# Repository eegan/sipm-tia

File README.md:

# sipm-tia
Transimpedance amplifiers for 4 SiPMs

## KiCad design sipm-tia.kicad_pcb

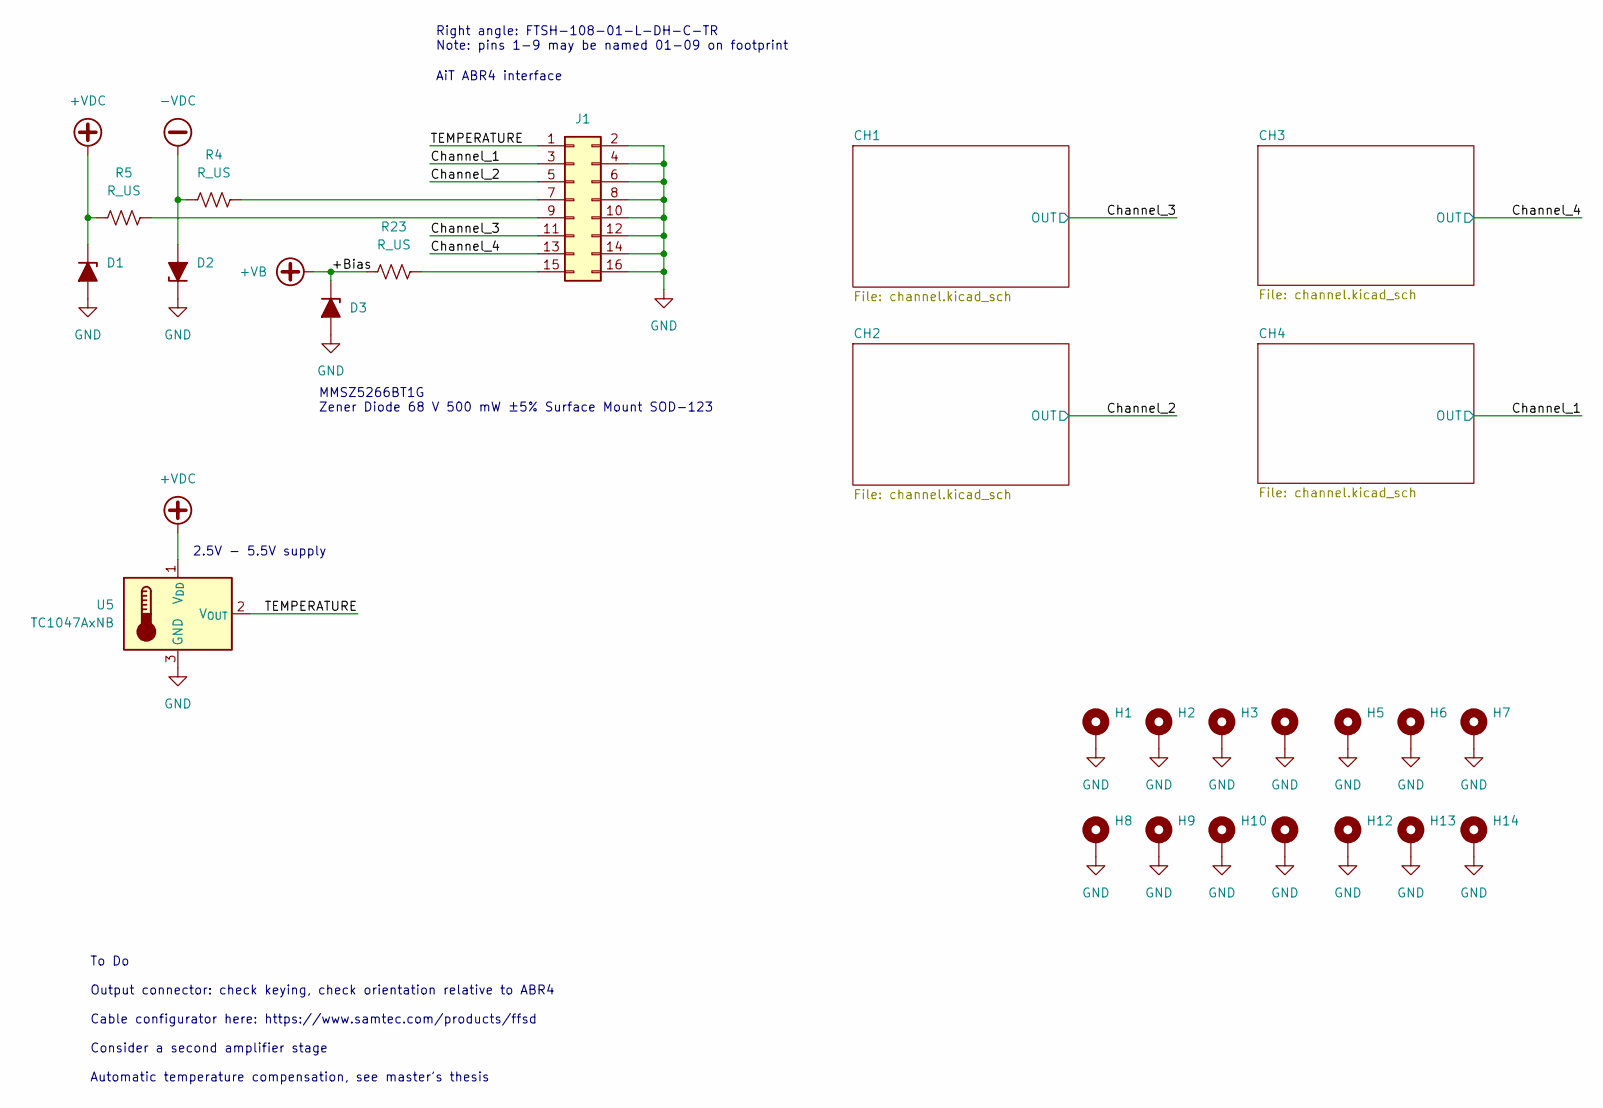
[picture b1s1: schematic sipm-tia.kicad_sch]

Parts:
D1, D2: D_Zener_Filled; D_SOD-123
D3: D_Zener_Filled; D_SOD-123; MPN MMSZ5266BT1G
H1, H2, H3, H4, H5, H6, H7, H8, H9, H10, H11, H12, H13, H14: MountingHole_Pad; MountingHole_3.2mm_M3_Pad
J1: Conn_02x08_Odd_Even; SAMTEC_FTSH-108-01-L-DH-C-TR; MPN FTSH-108-01-L-DH-C-TR
R4, R5, R23: R_US; R_0603_1608Metric
U5: TC1047AxNB; SOT-23; MPN TC1047AVNBTR

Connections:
+VB: D3.1 (K), R23.1; also elsewhere on the board
+VDC: D1.1 (K), R5.1, U5.1 (V_{DD}); also elsewhere on the board
-VDC: D2.2 (A), R4.1; also elsewhere on the board
/Channel_1: J1.3; also elsewhere on the board
/Channel_2: J1.5; also elsewhere on the board
/Channel_3: J1.11; also elsewhere on the board
/Channel_4: J1.13; also elsewhere on the board
/TEMPERATURE: J1.1, U5.2 (V_{OUT})
GND: D1.2 (A), D2.1 (K), D3.2 (A), H1.1, H2.1, H3.1, H4.1, H5.1, H6.1, H7.1, H8.1, H9.1, H10.1, H11.1, H12.1, H13.1, H14.1, J1.2, J1.4, J1.6, J1.8, J1.10, J1.12, J1.14, J1.16, U5.3 (GND); also elsewhere on the board
unnamed: J1.7, R4.2
unnamed: J1.9, R5.2
unnamed: J1.15, R23.2

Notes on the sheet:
To Do Output connector: check keying, check orientation relative to ABR4 Cable configurator here: https://www.samtec.com/products/ffsd Consider a second amplifier stage Automatic temperature compensation, see master's thesis
Right angle: FTSH-108-01-L-DH-C-TR Note: pins 1-9 may be named 01-09 on footprint
AiT ABR4 interface
2.5V - 5.5V supply
MMSZ5266BT1G Zener Diode 68 V 500 mW ±5% Surface Mount SOD-123

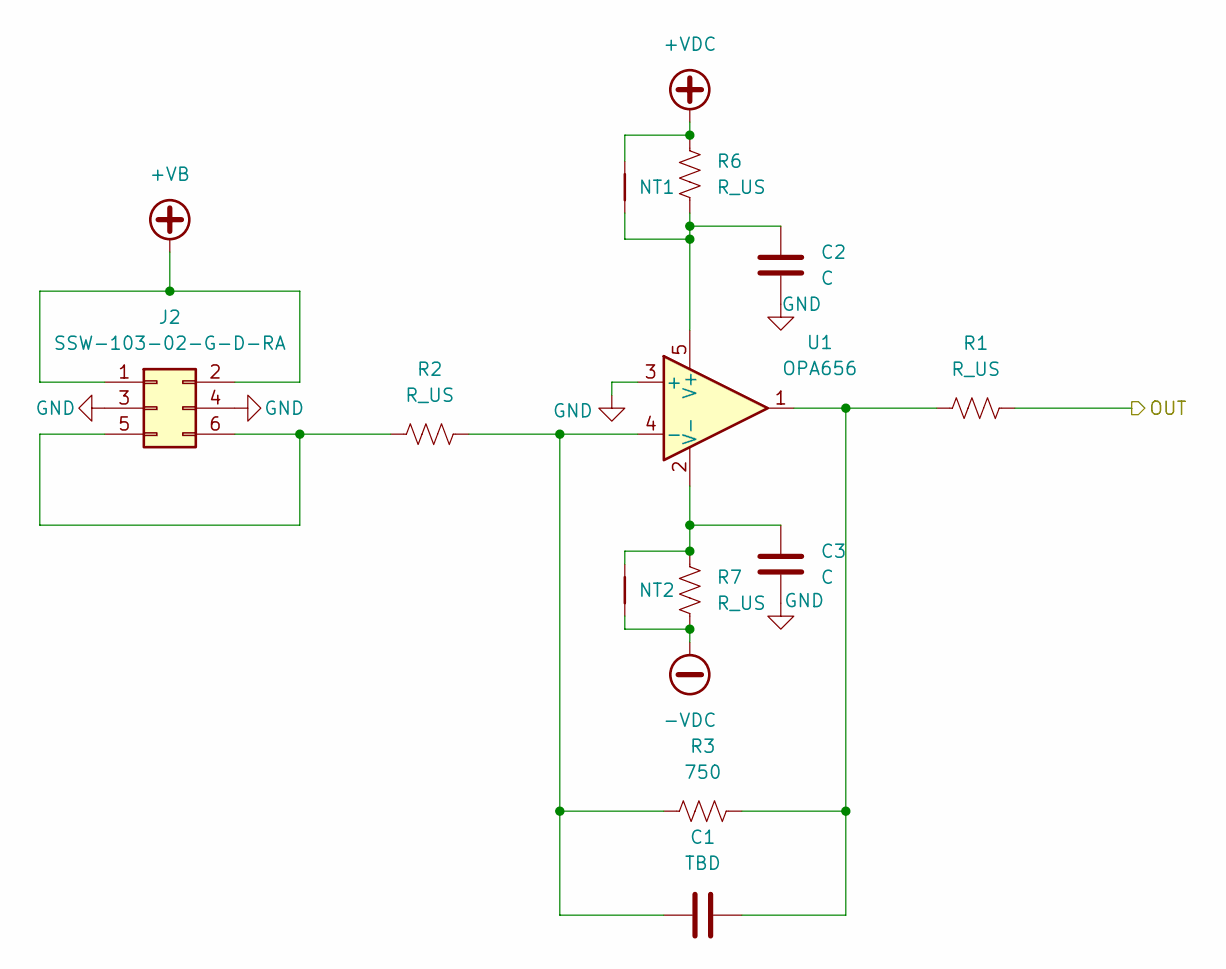
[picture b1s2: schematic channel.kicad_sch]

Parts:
C1: TBD; C_0603_1608Metric_Pad1.08x0.95mm_HandSolder
C2, C3: C; C_0603_1608Metric_Pad1.08x0.95mm_HandSolder
J2: SSW-103-02-G-D-RA; PinSocket_2x03_P2.54mm_Vertical; MPN SSW-103-02-G-D
NT1, NT2: NetTie_2; NetTie-2_SMD_Pad0.5mm
R1, R2, R6, R7: R_US; R_0603_1608Metric_Pad0.98x0.95mm_HandSolder
R3: 750; R_0603_1608Metric_Pad0.98x0.95mm_HandSolder
U1: OPA656; SOT-23-5

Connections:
+VB: J2.1, J2.2; also elsewhere on the board
+VDC: NT1.2, R6.2; also elsewhere on the board
-VDC: NT2.1, R7.1; also elsewhere on the board
/Channel_3: R1.2; also elsewhere on the board
GND: C2.1, C3.1, J2.3, J2.4, U1.3 (+); also elsewhere on the board
unnamed: C1.1, R1.1, R3.2, U1.1
unnamed: J2.5, J2.6, R2.1
unnamed: C1.2, R2.2, R3.1, U1.4 (-)
unnamed: C2.2, NT1.1, R6.1, U1.5 (V+)
unnamed: C3.2, NT2.2, R7.2, U1.2 (V-)

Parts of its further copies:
C4, C5, C7, C8, C10, C11: C; C_0603_1608Metric_Pad1.08x0.95mm_HandSolder
C6, C9, C12: TBD; C_0603_1608Metric_Pad1.08x0.95mm_HandSolder
J3, J4, J5: SSW-103-02-G-D-RA; PinSocket_2x03_P2.54mm_Vertical; MPN SSW-103-02-G-D
NT3, NT4, NT5, NT6, NT7, NT8: NetTie_2; NetTie-2_SMD_Pad0.5mm
R8, R9, R10, R11, R13, R14, R15, R16, R18, R19, R20, R21: R_US; R_0603_1608Metric_Pad0.98x0.95mm_HandSolder
R12, R17, R22: 750; R_0603_1608Metric_Pad0.98x0.95mm_HandSolder
U2, U3, U4: OPA656; SOT-23-5

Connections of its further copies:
+VB: J3.1, J3.2, J4.1, J4.2, J5.1, J5.2; also elsewhere on the board
+VDC: NT3.2, NT5.2, NT7.2, R8.2, R13.2, R18.2; also elsewhere on the board
-VDC: NT4.1, NT6.1, NT8.1, R11.1, R16.1, R21.1; also elsewhere on the board
/Channel_1: R19.2; also elsewhere on the board
/Channel_2: R9.2; also elsewhere on the board
/Channel_4: R14.2; also elsewhere on the board
GND: C4.1, C5.1, C7.1, C8.1, C10.1, C11.1, J3.3, J3.4, J4.3, J4.4, J5.3, J5.4, U2.3 (+), U3.3 (+), U4.3 (+); also elsewhere on the board
unnamed: C6.1, R9.1, R12.2, U2.1
unnamed: C9.1, R14.1, R17.2, U3.1
unnamed: C12.1, R19.1, R22.2, U4.1
unnamed: J3.5, J3.6, R10.1
unnamed: J4.5, J4.6, R15.1
unnamed: J5.5, J5.6, R20.1
unnamed: C6.2, R10.2, R12.1, U2.4 (-)
unnamed: C4.2, NT3.1, R8.1, U2.5 (V+)
unnamed: C5.2, NT4.2, R11.2, U2.2 (V-)
unnamed: C9.2, R15.2, R17.1, U3.4 (-)
unnamed: C7.2, NT5.1, R13.1, U3.5 (V+)
unnamed: C8.2, NT6.2, R16.2, U3.2 (V-)
unnamed: C12.2, R20.2, R22.1, U4.4 (-)
unnamed: C10.2, NT7.1, R18.1, U4.5 (V+)
unnamed: C11.2, NT8.2, R21.2, U4.2 (V-)

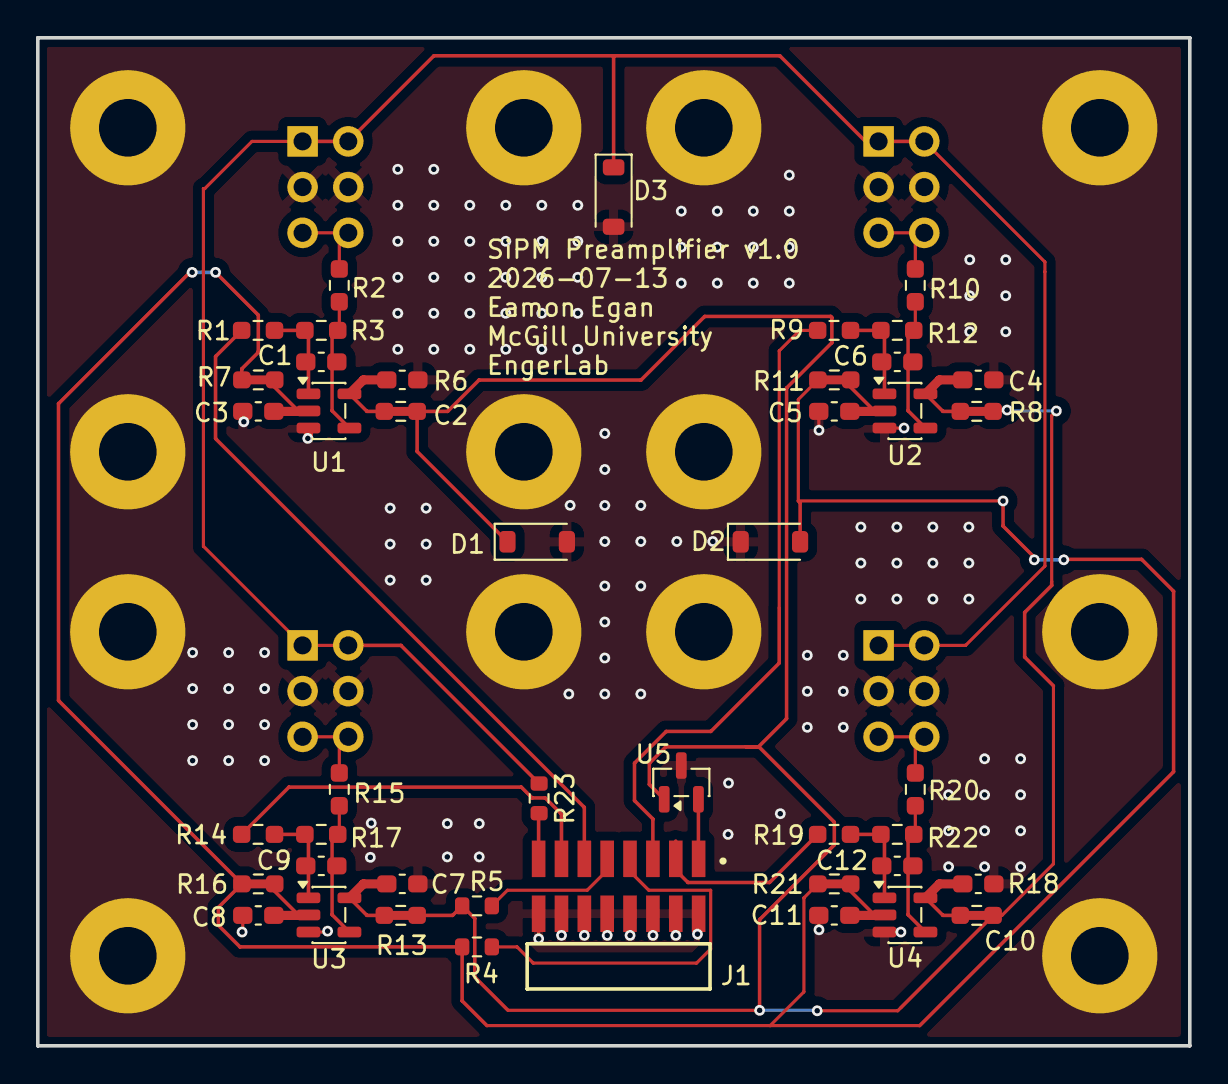
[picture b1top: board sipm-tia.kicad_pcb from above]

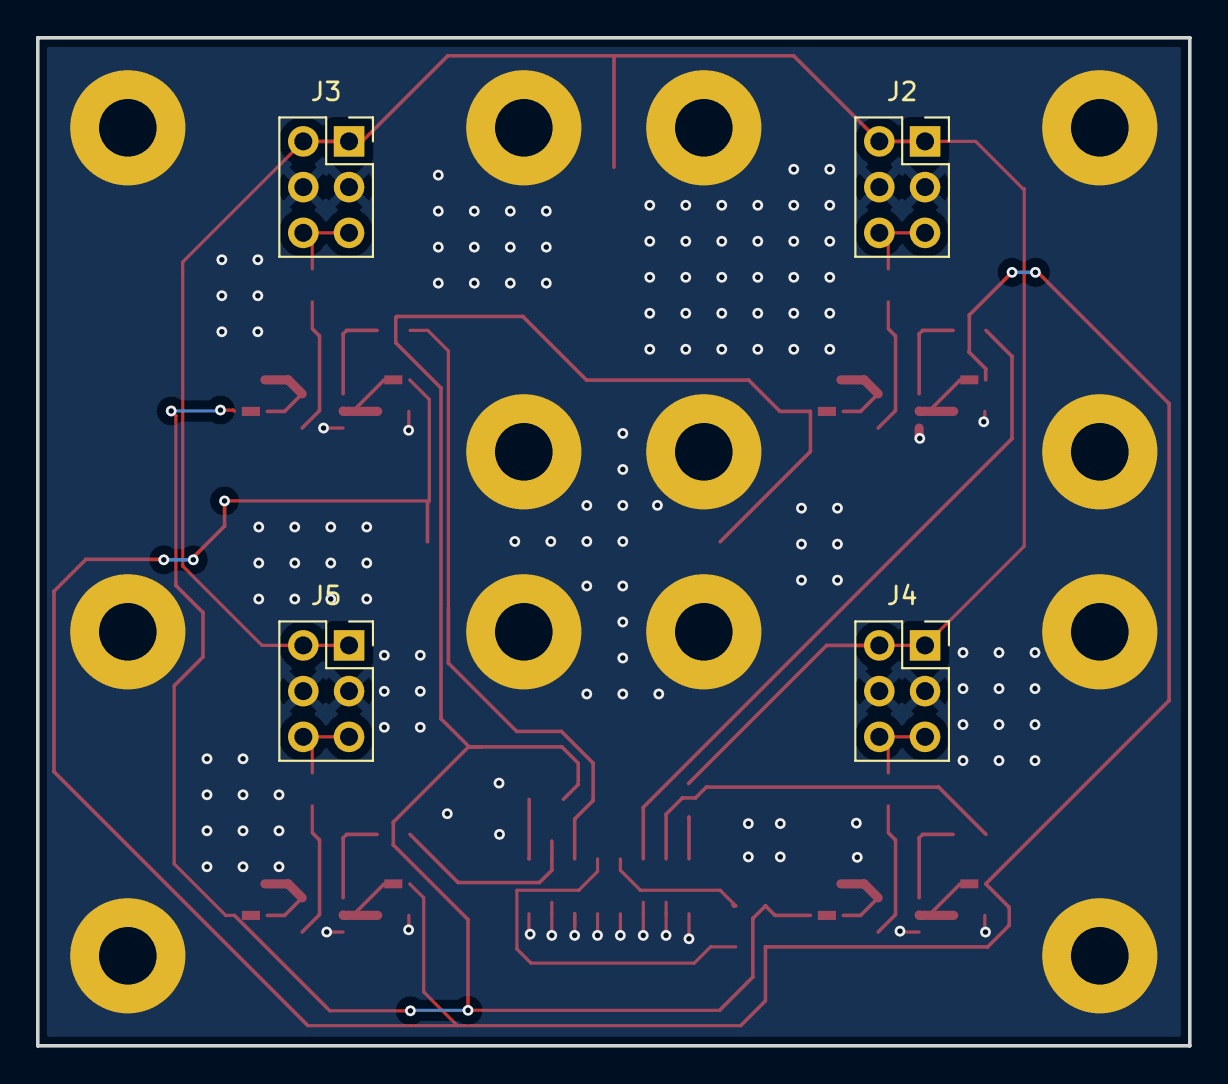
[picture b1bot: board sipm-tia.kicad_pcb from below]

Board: 2 copper layers, 64.0 x 56.0 mm, 69 parts (4 on the bottom side), 32 nets.
